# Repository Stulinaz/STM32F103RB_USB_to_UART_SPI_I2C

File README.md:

<!-- For .md file development refers to https://docs.github.com/en -->
# Stm32 Multiprotocol

> [!IMPORTANT]  
> Firmware rework scheduled by end of April 2025.

### Firmware and Kicad project for my USBtoUART/SPI/I2C converter.

Based on the popular microcontroller ***STM32F103RBT6*** and a custom PCB board.
This project is an embedded software/hardawe solutions that allows you to transfer data from USB to all the main digital interfaces - UART, I2C and SPI.
This board will help you to analyze and debug all the main digital and analog IC’s as well as lot of IOT and RF demoboard, saving you the time to develop a custom firmware
, or buying expensive data converters.

## Board Overview

## Top Side of the board

## Bottom Side of The board

## Features 

- SWD Interface.
- Mini USB Connector with ESD protection.
- Power mosfet.
- On board 64k (24C64) eeprom for data storage.

## Bill of Materials

| Component  | Description                      | Part Number              | Digy           |
|:---------  |:----------                       |:-------                  |:-------        |        
| USB1       | CONN RCPT USB2.0 MINI SMD R/A    | 0675031020               | [WM5461CT-ND](https://www.digikey.it/it/products/detail/molex/0675031020/1624424?s=N4IgTCBcDaIOoFkCsAWAbARgMIBUC0AcgCIgC6AvkA)                      |
| ESD1       | TVS DIODE 5.25V 17V STO23-6      | USBLC6-2SC6              | [497-5235-6-ND](https://www.digikey.it/it/products/detail/stmicroelectronics/USBLC6-2SC6/1040559)                                                   |
| ESD2       | TVS DIODE 5V SOT23-6]            | ESDA6V1BC6               | [497-6635-1-ND](https://www.digikey.it/it/products/detail/stmicroelectronics/ESDA6V1BC6/1037985?s=N4IgTCBcDaICwE4DsBaAbGgzAVhQRhQDkAREAXQF8g)       |
| U1         | Linear Voltage Regulator IC      | IC REG 3.3V 1A           | [576-1172-ND](https://www.digikey.it/it/products/detail/microchip-technology/MIC39100-3-3WS/771641?s=N4IgTCBcDaIKwHYBsBaAjGhYUDkAiIAugL5A)          |
| U2         | ic mcu 32 bit 128kb flash 64LQFP | STM32F103RBT6            | [497-6066-ND](https://www.digikey.it/it/products/detail/stmicroelectronics/STM32F103RBT6/1646341?s=N4IgTCBcDaICwE4DsBaAbABjWlA5AIiALoC%2BQA)        |
| Y2         | CRYSTAL 16.0000MHZ 4PF SMD       | ABM8W-16.0000MHZ-4-B1U-T3| [535-14020-1-ND](https://www.digikey.it/it/products/detail/abracon-llc/ABM8W-16-0000MHZ-4-B1U-T3/7172791?s=N4IgTCBcDaIKwGY4FoCMAWADGTbkDkAREAXQF8g) |
| U3         | IC GATE DRVR LOW-SIDE 8SOIC      | MIC4427ZM                | [576-3513-5-ND](https://www.digikey.it/it/products/detail/microchip-technology/MIC4427ZM/1029913?s=N4IgTCBcDaIKwHYBsBaAzHAjGlcUDkAREAXQF8g)         |
| U4         | IC GATE DRVR LOW-SIDE 8SOIC      | M24C64                   | [497-14427-1-ND](https://www.digikey.it/it/products/detail/stmicroelectronics/M24C64-DRMN3TP-K/4729231?s=N4IgTCBcDaICwE4DsBaAjHOZVpQOQBEQBdAXyA)    |     

## Software needed for development

- [STM32CubeIDE](https://www.st.com/en/development-tools/stm32cubeide.html) **1.17.0**
- [KICAD](https://www.kicad.org/) **8.0.5,release build - 64 bit**
- [GIT](https://git-scm.com/) **2.46.1.windows.1**

## Tools needed for development

Programmer [STLINK](https://www.st.com/en/development-tools/st-link-v2.html)

## Closeup

## Electrical Characteristics

| **Parameter**         | **Min** | **Typ** | **Max** | **Unit** | **Condition/Notes**   |
|-----------------------|---------|---------|---------|----------|-----------------------|
| Input Voltage         | 4.5     | 5.0     | 5.5     | V        |                       |
| Current Consumption   |         | 13      | 20      | mA       |                       |

## License

| Component                                    | Copyright                          | License                                          |
|:---------                                    |:----------                         |:-------                                          |
| CMSIS                                        | ARM Limited                        | Apache-2.0                                       |
| CMSIS Device                                 | ARM Limited - STMicroelectronics   | Apache-2.0                                       |
| STM32WL HAL                                  | STMicroelectronics                 | BSD-3-Clause                                     |
| FreeRTOS kernel                              | Amazon.com, Inc. or its affiliates | MIT                                              |
| Stm32 Multiprotocol                          | N/A                                | BSD-3-Clause                                     |

## Contact

***enrico.stulin@gmail.com***

[LinkedIn](https://www.linkedin.com/in/enrico-stulin-14090b146/)

## Important Information

> [!CAUTION]
> Manual soldering of SMD components requires high level of manual skills.
> Project not suited for beginners in firmware development.
> A good understanding of C language is a must.

> [!CAUTION]
> This project is provided "AS IS" with no warranties.

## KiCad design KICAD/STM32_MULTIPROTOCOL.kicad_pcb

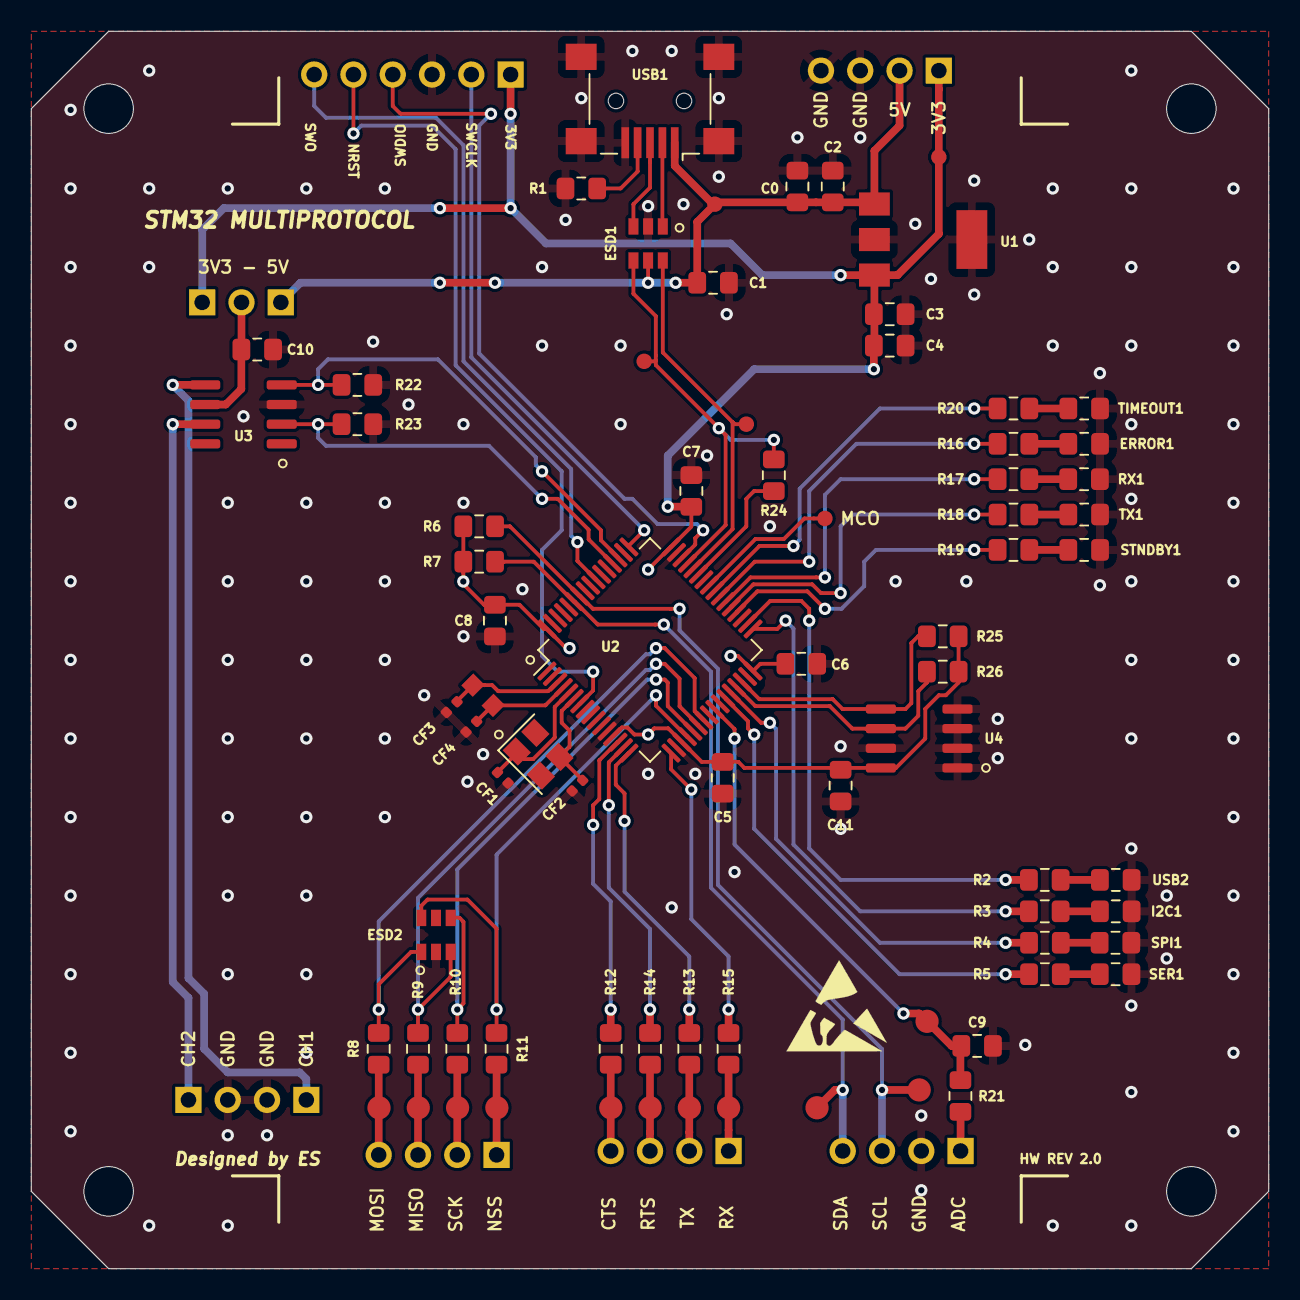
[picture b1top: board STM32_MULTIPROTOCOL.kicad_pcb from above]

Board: 2 copper layers, 80.0 x 80.0 mm, 83 parts (0 on the bottom side), 63 nets.

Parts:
C0, C1, C4, C5, C6, C7, C8, C10, C11: 100nF; R_0805_2012Metric_Pad1.15x1.40mm_HandSolder
C2: 1uF; R_0805_2012Metric_Pad1.15x1.40mm_HandSolder
C3, C9: 10uF; R_0805_2012Metric_Pad1.15x1.40mm_HandSolder
CF1, CF2, CF3, CF4: 22pF; R_0402_1005Metric
ERROR1: LED; R_0805_2012Metric_Pad1.15x1.40mm_HandSolder
ESD1: USBLC6-2SC6; SOT-23-6
ESD2: ESDA6V1BC6; SOT-23-6
I2C1: LED; R_0805_2012Metric_Pad1.15x1.40mm_HandSolder
I2C_OUT1: Conn_01x04; PinHeader_1x04_P2.54mm_Vertical
MCO1: TestPoint; TestPoint_Pad_D1.0mm
PROG1: Conn_01x06; PinHeader_1x06_P2.54mm_Vertical
PWR1: Conn_01x04; PinHeader_1x04_P2.54mm_Vertical
PWR_OUT1: Conn_01x04; PinHeader_1x04_P2.54mm_Vertical
PWR_SEL1: Conn_01x03; PinHeader_1x03_P2.54mm_Vertical
R1: 100k; R_0805_2012Metric_Pad1.15x1.40mm_HandSolder
R2, R3, R4, R5: 1k; R_0805_2012Metric_Pad1.15x1.40mm_HandSolder
R6, R7, R25, R26: 10k; R_0805_2012Metric_Pad1.15x1.40mm_HandSolder
R8, R9, R10, R11, R12, R13, R14, R15, R16, R17, R18, R19, R20, R21: 100R; R_0805_2012Metric_Pad1.15x1.40mm_HandSolder
R22, R23: 10kR; R_0805_2012Metric_Pad1.15x1.40mm_HandSolder
R24: 1.5k; R_0805_2012Metric_Pad1.15x1.40mm_HandSolder
RX1: LED; R_0805_2012Metric_Pad1.15x1.40mm_HandSolder
SER1: LED; R_0805_2012Metric_Pad1.15x1.40mm_HandSolder
SPI1: LED; R_0805_2012Metric_Pad1.15x1.40mm_HandSolder
SPI_OUT1: Conn_01x04; PinHeader_1x04_P2.54mm_Vertical
STNDBY1: LED; R_0805_2012Metric_Pad1.15x1.40mm_HandSolder
T1, T2, T3, T4: TestPoint; TestPoint_Pad_D1.0mm
T5, T6, T7, T8, T9, T10, T11, T12, T13, T14: TestPoint; TestPoint_Pad_D1.5mm
TIMEOUT1: LED; R_0805_2012Metric_Pad1.15x1.40mm_HandSolder
TP15: TestPoint; TestPoint_Pad_D1.5mm
TX1: LED; R_0805_2012Metric_Pad1.15x1.40mm_HandSolder
U1: MIC39100-3.3WS; SOT-223-3_TabPin2
U2: STM32F103R8Tx; LQFP-64_10x10mm_P0.5mm
U3: MIC4427; SOIC-8_3.9x4.9mm_P1.27mm
U4: M24C02-WMN; SOIC-8_3.9x4.9mm_P1.27mm
UART_OUT1: Conn_01x04; PinHeader_1x04_P2.54mm_Vertical
USB1: USB_B_Mini; USB_Mini-B_Lumberg_2486_01_Horizontal
USB2: LED; R_0805_2012Metric_Pad1.15x1.40mm_HandSolder
Y1: Crystal; Crystal_SMD_TXC_9HT11-2Pin_2.0x1.2mm_HandSoldering
Y2: Crystal_GND24; Crystal_SMD_3225-4Pin_3.2x2.5mm

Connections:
+3V3: C3.1, C4.1, C5.1, C6.1, C7.1, C8.1, C11.1, PROG1.6, PWR1.4, PWR_SEL1.1, R6.2, R7.2, R25.1, R26.1, T2.1, U1.3, U2.13, U2.19, U2.32, U2.48, U2.64, U4.8
ADC12_IN15_PIN25: C9.2, R21.2, TP15.1, U2.25
CH1_PWR: R22.1, U2.51, U3.4
CH2_PWR: R23.1, U2.52, U3.2
GND: C0.2, C1.2, C2.2, C3.2, C4.2, C5.2, C6.2, C7.2, C8.2, C9.1, C10.2, C11.2, CF1.2, CF2.2, CF3.2, CF4.2, ERROR1.1, ESD1.2, ESD2.2, ESD2.5, I2C1.1, I2C_OUT1.2, PROG1.4, PWR1.1, PWR1.2, PWR_OUT1.2, PWR_OUT1.3, R1.2, R22.2, R23.2, RX1.1, SER1.1, SPI1.1, STNDBY1.1, TIMEOUT1.1, TX1.1, U1.2, U2.12, U2.18, U2.31, U2.47, U2.63, U3.3, U4.1, U4.2, U4.3, U4.4, U4.7, USB1.5, USB1.6, USB2.1, Y2.2, Y2.4
I2C1_SCL_PB6_PIN58: I2C_OUT1.3, R6.1, T14.1, U2.58
I2C1_SDA_PB7_PIN59: I2C_OUT1.4, R7.1, T13.1, U2.59
I2C2_SCL_PB6_PIN58: R26.2, U2.29, U4.6
I2C2_SDA_PB7_PIN59: R25.2, U2.30, U4.5
NRST: PROG1.2, U2.7
unnamed: C10.1, PWR_SEL1.2, U3.6
unnamed: CF1.1, U2.5, Y2.1
unnamed: CF2.1, U2.6, Y2.3
unnamed: ERROR1.2, R16.1
unnamed: I2C1.2, R3.2
unnamed: I2C_OUT1.1, R21.1
unnamed: MCO1.1, U2.41
unnamed: PWR_OUT1.1, U3.7
unnamed: PWR_OUT1.4, U3.5
unnamed: R1.1, USB1.4
unnamed: R2.1, U2.34
unnamed: R2.2, USB2.2
unnamed: R3.1, U2.33
unnamed: R4.1, U2.28
unnamed: R4.2, SPI1.2
unnamed: R5.1, U2.27
unnamed: R5.2, SER1.2
unnamed: R8.1, SPI_OUT1.4, T5.1
unnamed: R9.1, SPI_OUT1.3, T6.1
unnamed: R10.1, SPI_OUT1.2, T7.1
unnamed: R11.1, SPI_OUT1.1, T8.1
unnamed: R12.1, T9.1, UART_OUT1.4
unnamed: R13.1, T11.1, UART_OUT1.2
unnamed: R14.1, T10.1, UART_OUT1.3
unnamed: R15.1, T12.1, UART_OUT1.1
unnamed: R16.2, U2.39
unnamed: R17.1, RX1.2
unnamed: R17.2, U2.38
unnamed: R18.1, TX1.2
unnamed: R18.2, U2.37
unnamed: R19.1, STNDBY1.2
unnamed: R20.1, TIMEOUT1.2
unnamed: R20.2, U2.40
unnamed: R24.1, U2.43
OSC32IN: CF3.1, U2.3, Y1.1
OSC32_OUT: CF4.1, U2.4, Y1.2
SPI1_MISO_PA6_PIN22: ESD2.3, R9.2, U2.22
SPI1_MOSI_PA7_PIN23: ESD2.1, R8.2, U2.23
SPI1_NSS_PA4_PIN20: ESD2.6, R11.2, U2.20
SPI1_SCK_PA5_PIN21: ESD2.4, R10.2, U2.21
STNDBY_LED: R19.2, U2.36
SWCLK_PA14_PIN49: PROG1.5, U2.49
SWDIO_PA13_PIN46: PROG1.3, U2.46
SWO_PB3_PIN55: PROG1.1, U2.55
UART2_CTS_PA0_PIN14: R12.2, U2.14
UART2_RTS_PA1_PIN15: R14.2, U2.15
UART2_RX_PA3_PIN17: R15.2, U2.17
UART2_TX_PA2_PIN16: R13.2, U2.16
USBDM: ESD1.1, USB1.2
USBDP: ESD1.3, USB1.3
USB_DATA+: ESD1.4, R24.2, T3.1, U2.45
USB_DATA-: ESD1.6, T4.1, U2.44
VUSB: C0.1, C1.1, C2.1, ESD1.5, PWR1.3, PWR_SEL1.3, T1.1, U1.1, USB1.1

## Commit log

2021-11-24 uart,spi,iic pins init in input mode. USB enable fixed.
2021-11-25 added command "stm-testled" for soldering, added schematic.pdf
2021-11-25 added tim 4 and command reference.docx, fixed app_usb
2021-11-25 added detailed BOM of the boards
2021-11-29 added driver for MIPOT TRX module 32001270/32001534
2021-12-20 tx/rx led fixed, uart rx data streming fixed
2022-01-11 added pcb revision 2, fixed firmware project for cloners
2022-01-15 added rev 2 BOM, added driver for onboard 24C64 eeprom, improved app_usb
2022-01-15 added contact for information and samples
2022-01-20 device reads and store its uptime in eeprom
2022-01-23 improved buffer manger, increased txrx vcp buffer to 1000
2022-02-11 improved power consumption, developing driver for oled display SSD1306
2022-03-03 ssd1306 driver is working, improved power consumption
2022-03-26 small improvements
2025-03-11 directory redefined, scheduled fw rework
2025-03-12 updated to kicad 8
2025-03-12 added freertos
2025-03-12 added contact information - removed rev 1
